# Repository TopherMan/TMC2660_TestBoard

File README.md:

Overview
=======
Board for testing out Trinamic's TMC2660.

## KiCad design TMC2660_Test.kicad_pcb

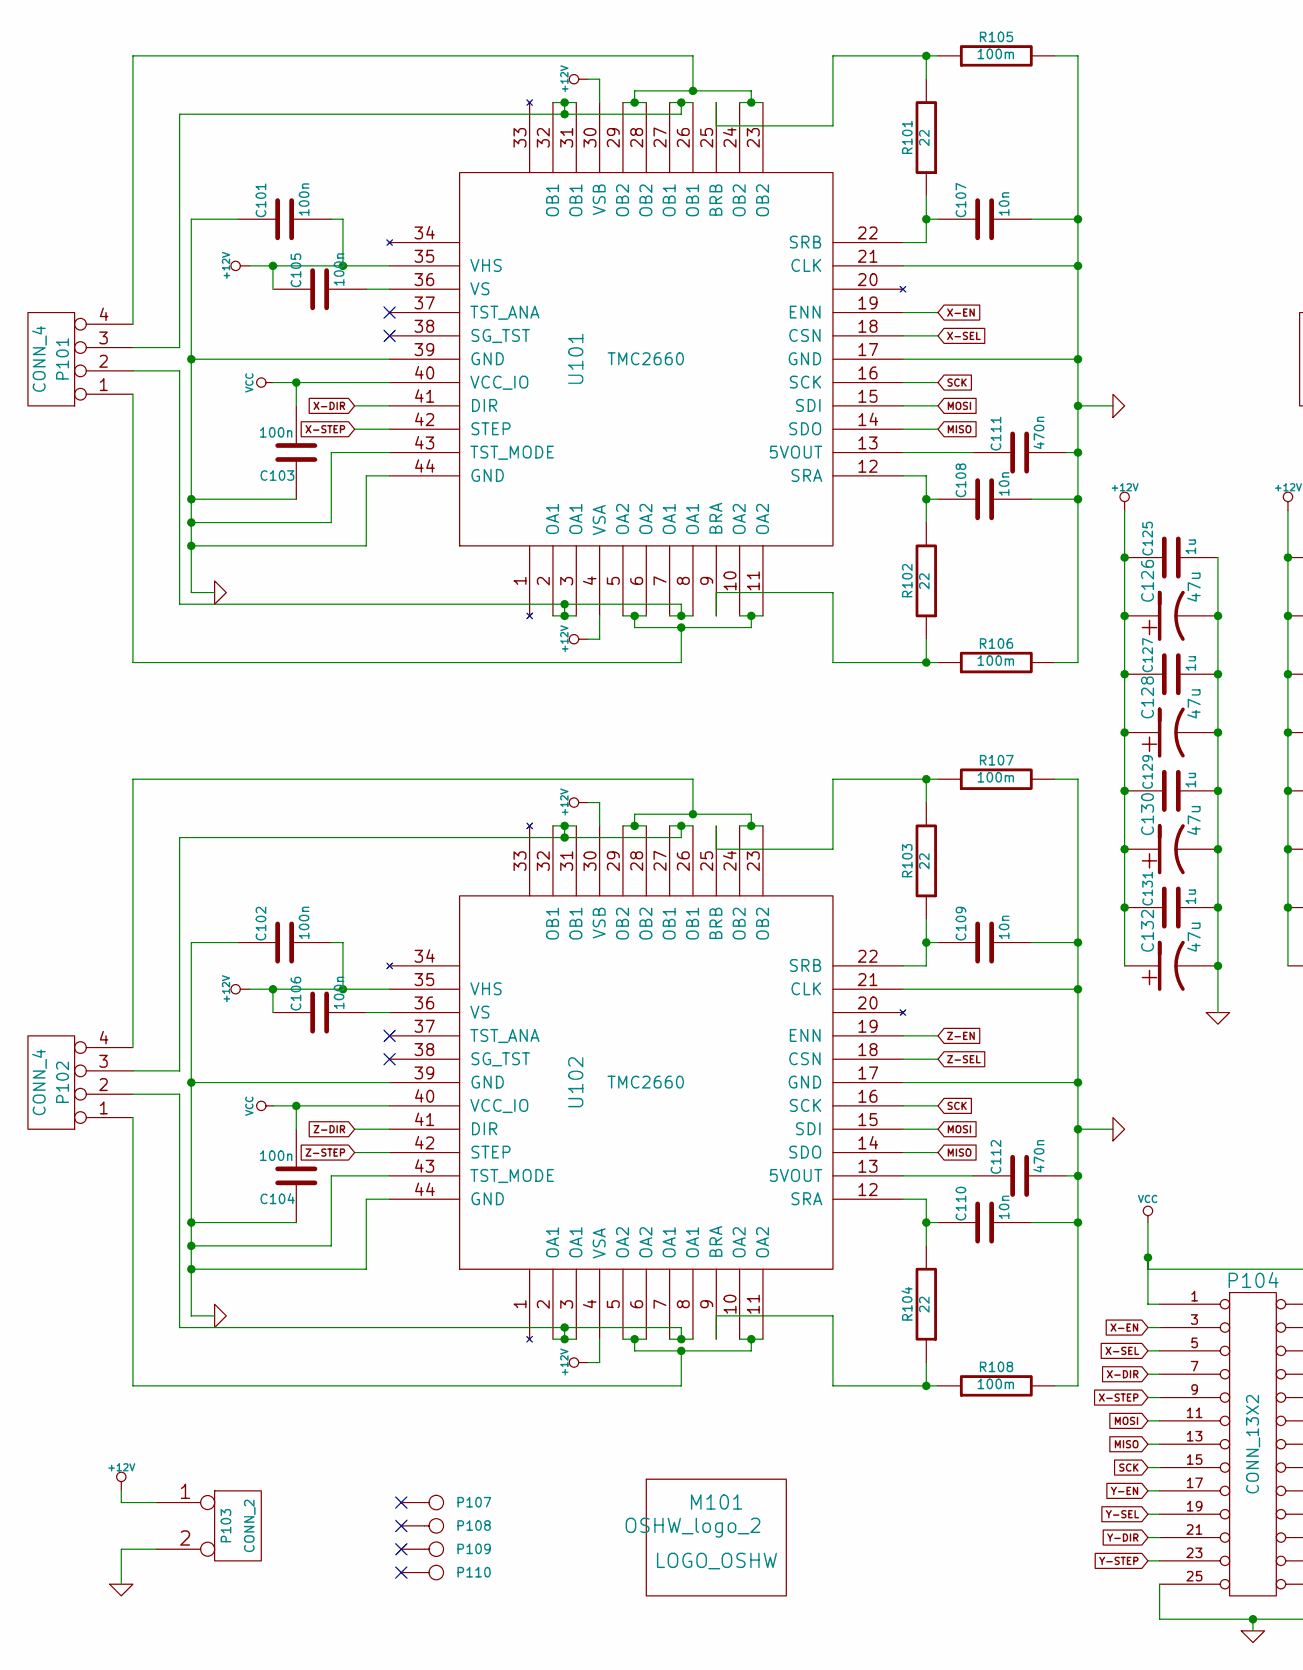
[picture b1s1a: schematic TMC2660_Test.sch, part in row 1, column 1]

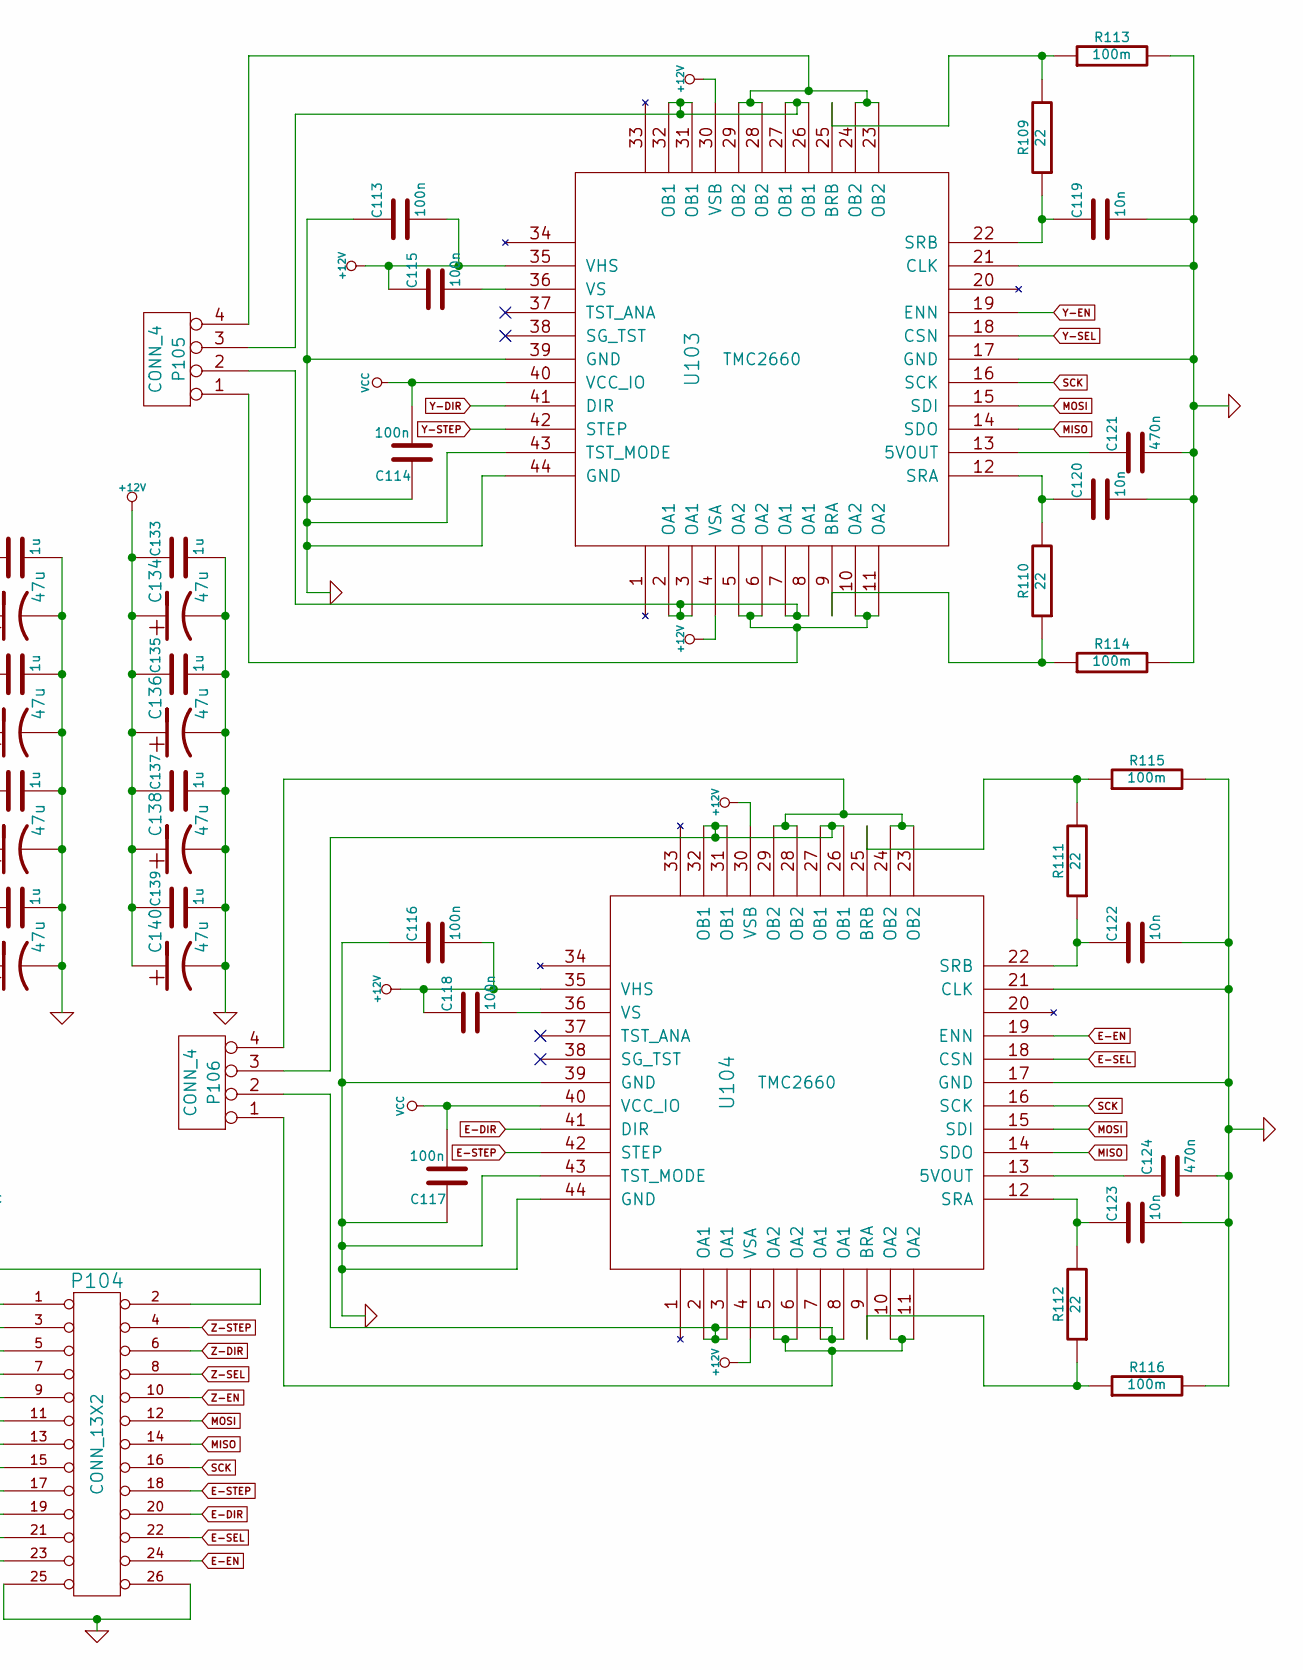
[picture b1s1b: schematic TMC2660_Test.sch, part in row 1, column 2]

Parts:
C101, C102, C103, C104, C105, C106, C113, C114, C115, C116, C117, C118: 100n
C107, C108, C109, C110, C119, C120, C122, C123: 10n
C111, C112, C121, C124: 470n
C125, C127, C129, C131, C133, C135, C137, C139: 1u
C126, C128, C130, C132, C134, C136, C138, C140: 47u
M101: LOGO_OSHW; OSHW_logo_2
P101, P102, P105, P106: CONN_4
P103: CONN_2
P104: CONN_13X2
P107, P108, P109, P110: CONN_1
R101, R102, R103, R104, R109, R110, R111, R112: 22
R105, R106, R107, R108, R113, R114, R115, R116: 100m
U101, U102, U103, U104: TMC2660

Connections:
+12V: C101.2, C102.2, C105.1, C106.1, C113.2, C115.1, C116.2, C118.1, C125.1, C126.1, C127.1, C128.1, C129.1, C130.1, C131.1, C132.1, C133.1, C134.1, C135.1, C136.1, C137.1, C138.1, C139.1, C140.1, P103.1, U101.4 (VSA), U101.30 (VSB), U101.35 (VHS), U102.4 (VSA), U102.30 (VSB), U102.35 (VHS), U103.4 (VSA), U103.30 (VSB), U103.35 (VHS), U104.4 (VSA), U104.30 (VSB), U104.35 (VHS)
E-DIR: P104.20, U104.41 (DIR)
E-EN: P104.24 (P20), U104.19 (ENN)
E-SEL: P104.22, U104.18 (CSN)
E-STEP: P104.18, U104.42 (STEP)
GND: C101.1, C102.1, C103.1, C104.1, C107.2, C108.2, C109.2, C110.2, C111.2, C112.2, C113.1, C114.1, C116.1, C117.1, C119.2, C120.2, C121.2, C122.2, C123.2, C124.2, C125.2, C126.2, C127.2, C128.2, C129.2, C130.2, C131.2, C132.2, C133.2, C134.2, C135.2, C136.2, C137.2, C138.2, C139.2, C140.2, P103.2 (PM), P104.25 (P24), P104.26 (P22), R105.2, R106.2, R107.2, R108.2, R113.2, R114.2, R115.2, R116.2, U101.17 (GND), U101.21 (CLK), U101.39 (GND), U101.43 (TST_MODE), U101.44 (GND), U102.17 (GND), U102.21 (CLK), U102.39 (GND), U102.43 (TST_MODE), U102.44 (GND), U103.17 (GND), U103.21 (CLK), U103.39 (GND), U103.43 (TST_MODE), U103.44 (GND), U104.17 (GND), U104.21 (CLK), U104.39 (GND), U104.43 (TST_MODE), U104.44 (GND)
MISO: P104.13, P104.14, U101.14 (SDO), U102.14 (SDO), U103.14 (SDO), U104.14 (SDO)
MOSI: P104.11, P104.12, U101.15 (SDI), U102.15 (SDI), U103.15 (SDI), U104.15 (SDI)
unnamed: C118.2, U104.36 (VS)
unnamed: P106.3, U104.26 (OB1), U104.27 (OB1), U104.31 (OB1), U104.32 (OB1)
unnamed: C123.1, R112.2, U104.12 (SRA)
unnamed: C124.1, U104.13 (5VOUT)
unnamed: C122.1, R111.1, U104.22 (SRB)
unnamed: P106.2, U104.2 (OA1), U104.3 (OA1), U104.7 (OA1), U104.8 (OA1)
unnamed: C120.1, R110.2, U103.12 (SRA)
unnamed: C121.1, U103.13 (5VOUT)
unnamed: C119.1, R109.1, U103.22 (SRB)
unnamed: R109.2, R113.1, U103.25 (BRB)
unnamed: R110.1, R114.1, U103.9 (BRA)
unnamed: P105.2, U103.2 (OA1), U103.3 (OA1), U103.7 (OA1), U103.8 (OA1)
unnamed: P105.3, U103.26 (OB1), U103.27 (OB1), U103.31 (OB1), U103.32 (OB1)
unnamed: P105.1, U103.5 (OA2), U103.6 (OA2), U103.10 (OA2), U103.11 (OA2)
unnamed: P105.4, U103.23 (OB2), U103.24 (OB2), U103.28 (OB2), U103.29 (OB2)
unnamed: P106.1, U104.5 (OA2), U104.6 (OA2), U104.10 (OA2), U104.11 (OA2)
unnamed: P106.4, U104.23 (OB2), U104.24 (OB2), U104.28 (OB2), U104.29 (OB2)
unnamed: R111.2, R115.1, U104.25 (BRB)
unnamed: R112.1, R116.1, U104.9 (BRA)
unnamed: R102.1, R106.1, U101.9 (BRA)
unnamed: C107.1, R101.1, U101.22 (SRB)
unnamed: R101.2, R105.1, U101.25 (BRB)
unnamed: C108.1, R102.2, U101.12 (SRA)
unnamed: C111.1, U101.13 (5VOUT)
unnamed: C112.1, U102.13 (5VOUT)
unnamed: P101.1, U101.5 (OA2), U101.6 (OA2), U101.10 (OA2), U101.11 (OA2)
unnamed: P101.3, U101.26 (OB1), U101.27 (OB1), U101.31 (OB1), U101.32 (OB1)
unnamed: C105.2, U101.36 (VS)
unnamed: P101.4, U101.23 (OB2), U101.24 (OB2), U101.28 (OB2), U101.29 (OB2)
unnamed: P101.2, U101.2 (OA1), U101.3 (OA1), U101.7 (OA1), U101.8 (OA1)
unnamed: C115.2, U103.36 (VS)
unnamed: P102.3, U102.26 (OB1), U102.27 (OB1), U102.31 (OB1), U102.32 (OB1)
unnamed: P102.2, U102.2 (OA1), U102.3 (OA1), U102.7 (OA1), U102.8 (OA1)
unnamed: P102.1, U102.5 (OA2), U102.6 (OA2), U102.10 (OA2), U102.11 (OA2)
unnamed: C106.2, U102.36 (VS)
unnamed: R103.2, R107.1, U102.25 (BRB)
unnamed: R104.1, R108.1, U102.9 (BRA)
unnamed: C110.1, R104.2, U102.12 (SRA)
unnamed: C109.1, R103.1, U102.22 (SRB)
unnamed: P102.4, U102.23 (OB2), U102.24 (OB2), U102.28 (OB2), U102.29 (OB2)
SCK: P104.15, P104.16, U101.16 (SCK), U102.16 (SCK), U103.16 (SCK), U104.16 (SCK)
VCC: C103.2, C104.2, C114.2, C117.2, P104.1, P104.2, U101.40 (VCC_IO), U102.40 (VCC_IO), U103.40 (VCC_IO), U104.40 (VCC_IO)
X-DIR: P104.7, U101.41 (DIR)
X-EN: P104.3, U101.19 (ENN)
X-SEL: P104.5, U101.18 (CSN)
X-STEP: P104.9, U101.42 (STEP)
Y-DIR: P104.21, U103.41 (DIR)
Y-EN: P104.17, U103.19 (ENN)
Y-SEL: P104.19, U103.18 (CSN)
Y-STEP: P104.23, U103.42 (STEP)
Z-DIR: P104.6, U102.41 (DIR)
Z-EN: P104.10, U102.19 (ENN)
Z-SEL: P104.8, U102.18 (CSN)
Z-STEP: P104.4, U102.42 (STEP)

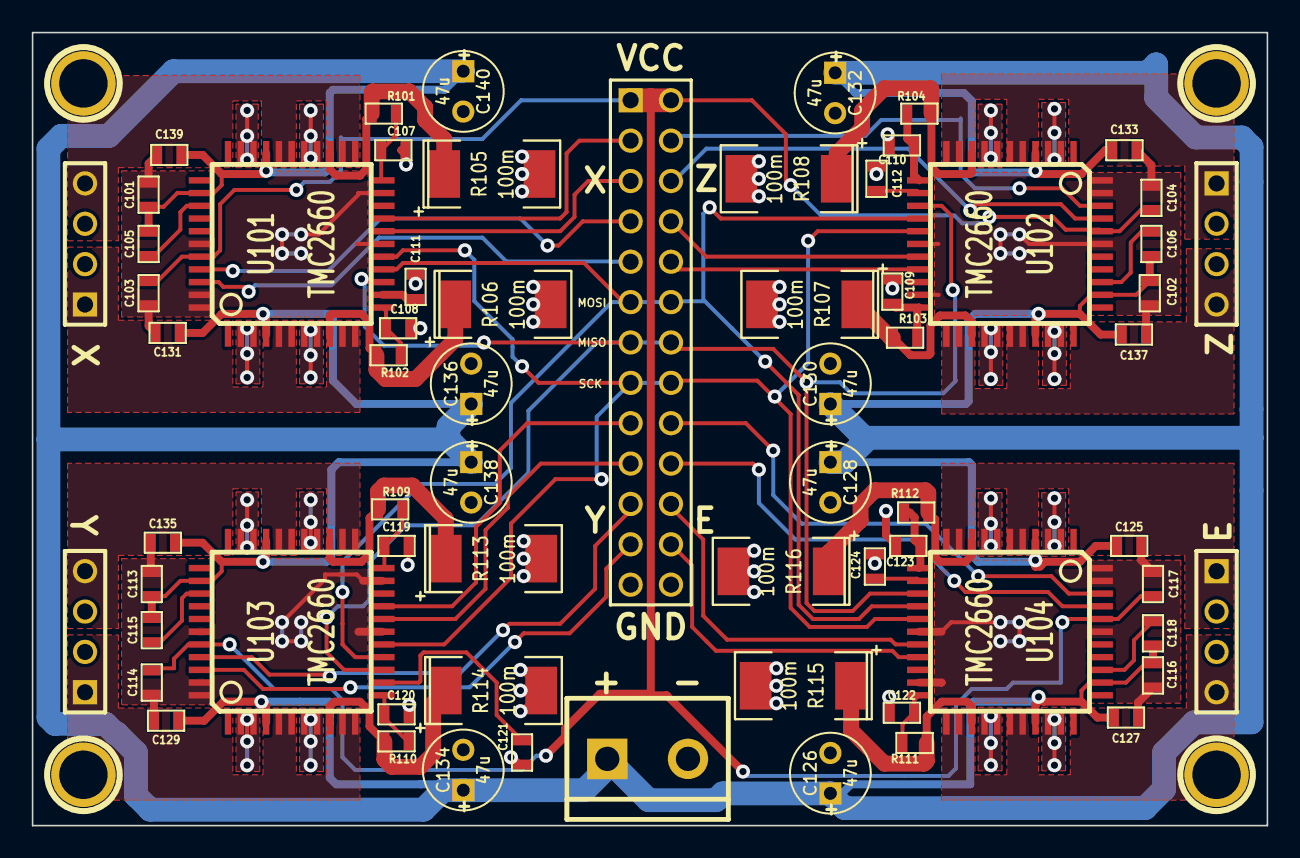
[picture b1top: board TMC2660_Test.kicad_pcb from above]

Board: 2 copper layers, 77.7 x 49.9 mm, 71 parts (1 on the bottom side), 62 nets.

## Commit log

2014-04-05 Init project.
2014-04-05 Add library and begin.
2014-04-05 Schematic for chips.
2014-04-05 First schematic complete, netlist generated.
2014-04-05 Fix a stupid copy-paste error.
2014-04-05 Associate footprints.
2014-04-06 Begin layout. About halfway there.
2014-04-06 Halfway done with layout.
2014-04-06 Adjust connector to match other side.
2014-04-06 Fixed a few oopsies.
2014-04-06 Layout work.
2014-04-07 Placements and most of routing done.
2014-04-07 Adjust netlist for easier layout.
2014-04-07 First attempt at layout complete.
2014-04-07 Cleanup, fix an oopsie.
2014-04-07 Few more fixes.
2014-04-08 Add mounting holes, dummy.
2014-04-08 Mount holes added to board, paths adjusted.
2014-05-05 Darn, need 2512's for the sense resistors.
2014-05-05 Removed pcb, starting from scratch.
2014-05-05 Add decoupling caps--one ceramic and one electrolytic per driver.
2014-05-05 Footprint associations. Replace 0805 components with 0603.
2014-05-05 Begin layout.
2014-05-08 Change alu. caps to thru hole.
2014-05-08 One chip sorta laid out.
2014-05-11 Added more capacitors!
2014-05-12 Getting the layout close to complete
2014-05-23 Everything is approximately where it should be. Now to draw all the damn fills and lines.
2014-05-23 Work on filled zones.
2014-05-23 Fixed weird error.
2014-05-30 Finished all the power connections and varios R and Cs connected to the chips. Still to do: ground plane, signal lines, connect motor planes properly.
2014-05-30 Add ground plane, begin adding signal traces.
2014-05-30 Getting pretty close.
2014-05-31 Layout complete! (maybe)
2014-05-31 Moved referenes around so you'll see them when it's made.
2014-05-31 Added some notes, labels on silkscreen, and Open Source Hardware logo.
2014-05-31 Begin bill of materials.
2014-06-04 Damn, got the input protection resistors wrong (placement and value). Now fixed.
2014-06-04 Begin fixing tracks, and fix stupid fill errors.
2014-06-04 Tracks half fixed. Considering dumping input protection.
2014-08-15 Fix resistors, beef up current detection traces.
